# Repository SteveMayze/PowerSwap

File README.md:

# PowerSwap
A Power control module for the Roll With it Project

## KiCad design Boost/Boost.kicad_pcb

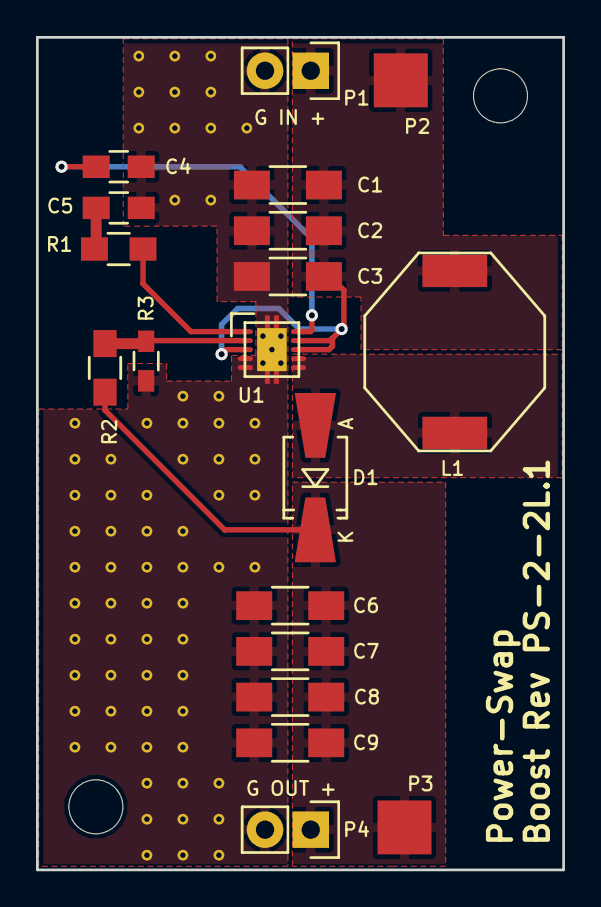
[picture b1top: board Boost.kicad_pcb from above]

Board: 2 copper layers, 29.2 x 46.3 mm, 19 parts (0 on the bottom side), 8 nets.

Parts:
C1, C2, C3, C6, C7, C8, C9: 10μF; C_1206_HandSoldering
C4: 100nF; C_0805_HandSoldering
C5: 820pF; C_0805_HandSoldering
D1: 0.45V; SMA-SMB_Universal_Handsoldering
L1: 4.70H; SRU1048-4R7Y
P1, P4: CONN_01X02; Pin_Header_Straight_1x02
P2, P3: TST; Measurement_Point_Square-SMD-Pad_Big
R1: 57.6KΩ; R_0805_HandSoldering
R2: 150KΩ; R_0805_HandSoldering
R3: 39KΩ; R_0603_HandSoldering
U1: TSP61087; TPS61087DSCR

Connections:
/Comp: R1.1, U1.1
/FB: R2.2, R3.1, U1.2
/Lin: C1.1, C2.1, C3.1, L1.1, P1.1, P2.1, U1.3, U1.8, U1.9
/Lout: D1.2, L1.2, U1.6, U1.7
/SS: C4.1, U1.10
/Vout: C6.1, C7.1, C8.1, C9.1, D1.1, P3.1, P4.1, R2.1
GND: C1.2, C2.2, C3.2, C4.2, C5.2, C6.2, C7.2, C8.2, C9.2, P1.2, P4.2, R3.2, U1.4, U1.5, U1.11
unnamed: C5.1, R1.2

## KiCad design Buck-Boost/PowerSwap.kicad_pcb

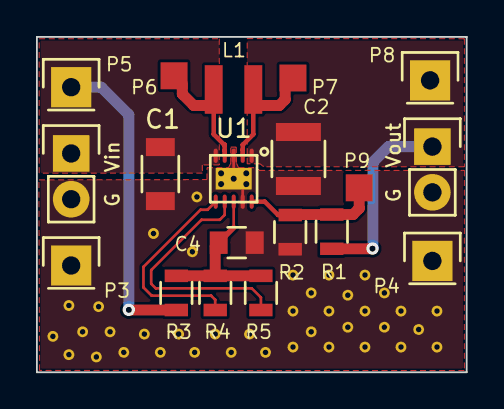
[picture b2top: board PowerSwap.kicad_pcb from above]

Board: 2 copper layers, 23.9 x 18.6 mm, 19 parts (0 on the bottom side), 9 nets.

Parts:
C1: 4.7μF; C_1206
C2: 22μF; C_1210
C4: 0.1μF; C_0805
L1: 2.2μΗ; SRN3015
P1: Battery; Pin_Header_Straight_1x02
P2: Vout; Pin_Header_Straight_1x02
P3, P4, P5, P8: TST; Pin_Header_Straight_1x01
P6, P7, P9: TST; Measurement_Point_Square-SMD-Pad_Small
R1: 1.2MΩ; R_0805
R2: 215KΩ; R_0805
R3, R4, R5: 0; R_0805
U1: TPS63030

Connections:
/EN: R4.1, U1.6
/Feedback: P9.1, R1.2, R2.1, U1.10
/L1: L1.1, P6.1, U1.4
/L2: L1.2, P7.1, U1.2
/PS: R5.1, U1.7
/Vin+: C1.1, P1.1, P5.1, R3.2, U1.5
/Vina: C4.1, R3.1, R4.2, R5.2, U1.8
/Vout+: C2.1, P2.1, P8.1, R1.1, U1.1
GNDPWR: C1.2, C2.2, C4.2, P1.2, P2.2, P3.1, P4.1, R2.2, U1.3, U1.9, U1.11

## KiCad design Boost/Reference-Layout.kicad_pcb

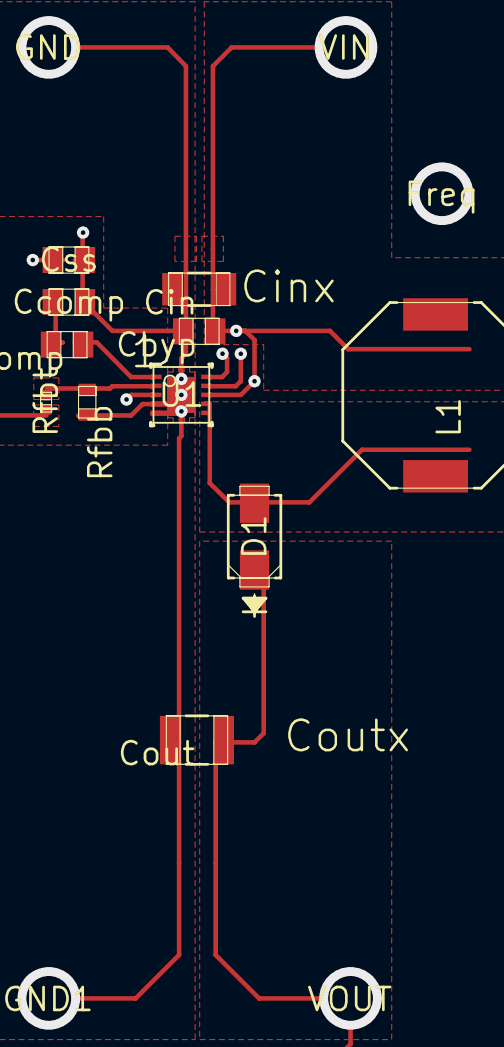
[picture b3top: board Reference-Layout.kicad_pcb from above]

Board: 10 copper layers, 16 parts (0 on the bottom side), 9 nets.

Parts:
Cbyp: 0805
Ccomp: 0805
Cin: 1206
Cout: 1210
Css: 0805
D1: SMA
Freq: TP-1502
GND, GND1: TP-1502
L1: SRU1048
Rcomp: 0805
Rfbb: 0603
Rfbt: 0402
U1: DSC0010A
VIN: TP-1502
VOUT: TP-1502

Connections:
0: Cbyp.2, Ccomp.2, Cin.2, Cout.2, Css.2, GND.1, GND1.1, Rfbb.2, U1.4, U1.5, U1.11
1: Cbyp.1, Cin.1, L1.1, U1.3, U1.8, VIN.1
2: Cout.1, D1.1, Rfbt.1, VOUT.1
4: D1.2, L1.2, U1.6, U1.7
5: Rcomp.1, U1.1
6: Rfbb.1, Rfbt.2, U1.2
7: Ccomp.1, Rcomp.2
10: Css.1, U1.10
11: Freq.1, U1.9

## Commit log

2015-08-01 Created the project and project sturcture
2015-08-01 Added a datasheet
2015-08-01 Added schematic for the power regulator
2015-08-01 Added a spreadsheet for calculating the component values
2015-08-02 Touched up the labeling of the schematic test points and wires
2015-08-10 Added a open office component values spreadsheet
2015-08-11 Updated the component calculations
2015-08-11 Added a data sheet
2015-08-18 Added footprints for inductor and power converter
2015-08-18 Started the layout
2015-08-18 Added a couple of datasheets
2015-08-24 Completed layout
2015-08-27 Final layout
2015-08-28 Completed the layout and gerbers
2015-09-23 Added a layout image
2015-10-22 Added some testing info and corrections
2015-10-22 Added BOM
2015-10-22 Fixed the TPS63030 footprint and cleaned up the layout
2015-10-22 Created Gerbers for 2L.2-c220856
2015-10-22 Added tracks to GND of the TPS63030
2015-10-22 Layout image for Rev2
2015-10-29 Moved the kicad to Buck-Boost and created the Boost directory
2015-10-29 Added the reference layout and created the initial schematic based on the reference circuit
2015-11-02 Created the foot prints for the inductor and regulator and imported to the PCB
2015-11-03 Components in position for the layout
2015-11-03 Added power planes for the layout
2015-11-03 Added routing to the layout
2015-11-03 Added stitching and labels
2015-11-04 Added the layout diagram and updated the version information on the board
2015-11-04 Created Gerbers and stinsil file
2015-11-05 Cleaned up the layout in preperation for gerbers. Made some pads solid rather than from parent
2015-11-05 Finalised the gerbers
2015-11-05 Added the OSHPark order details and layout graphic
2015-11-20 Added photos of reflow efforts on Rev2
2015-11-20 Added text annotations for input and output voltage
2015-11-20 Added initial documentation for the usage and test results
2015-11-29 Corrected C3 from 10uF to 1uF
2015-11-29 Finalised the result data for the buck-boost data sheet
2015-11-29 Updated the testing results for buck-boost and boost
